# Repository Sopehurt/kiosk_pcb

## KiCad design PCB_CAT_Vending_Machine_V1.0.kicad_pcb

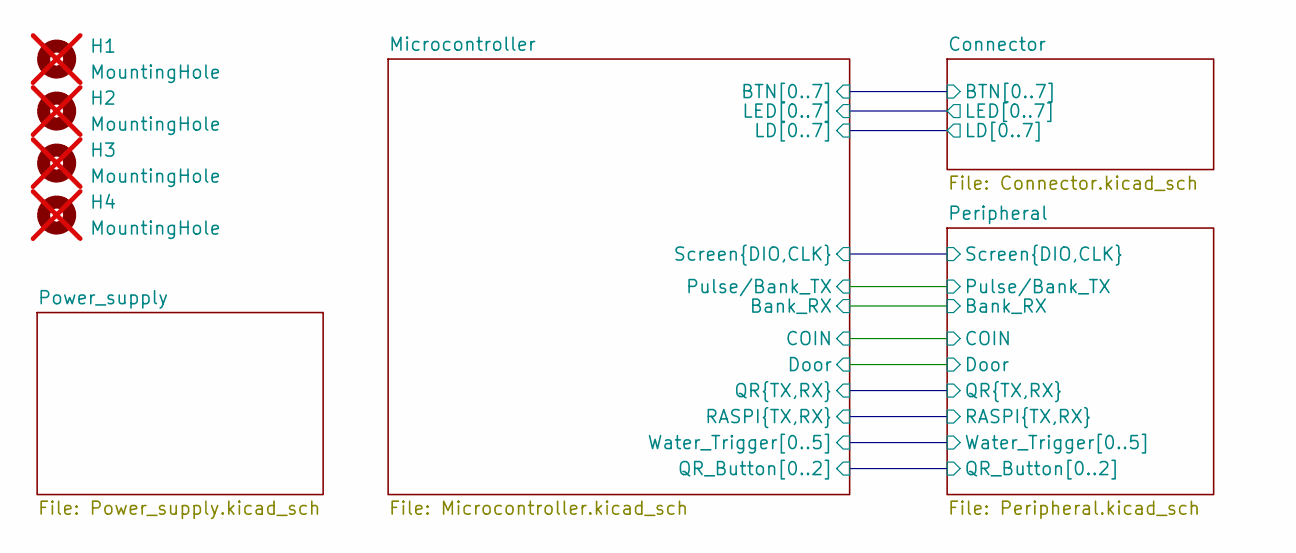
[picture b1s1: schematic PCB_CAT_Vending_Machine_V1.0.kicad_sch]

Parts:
H1, H2, H3, H4: MountingHole; MountingHole_3.2mm_M3_Pad_TopBottom; not fitted

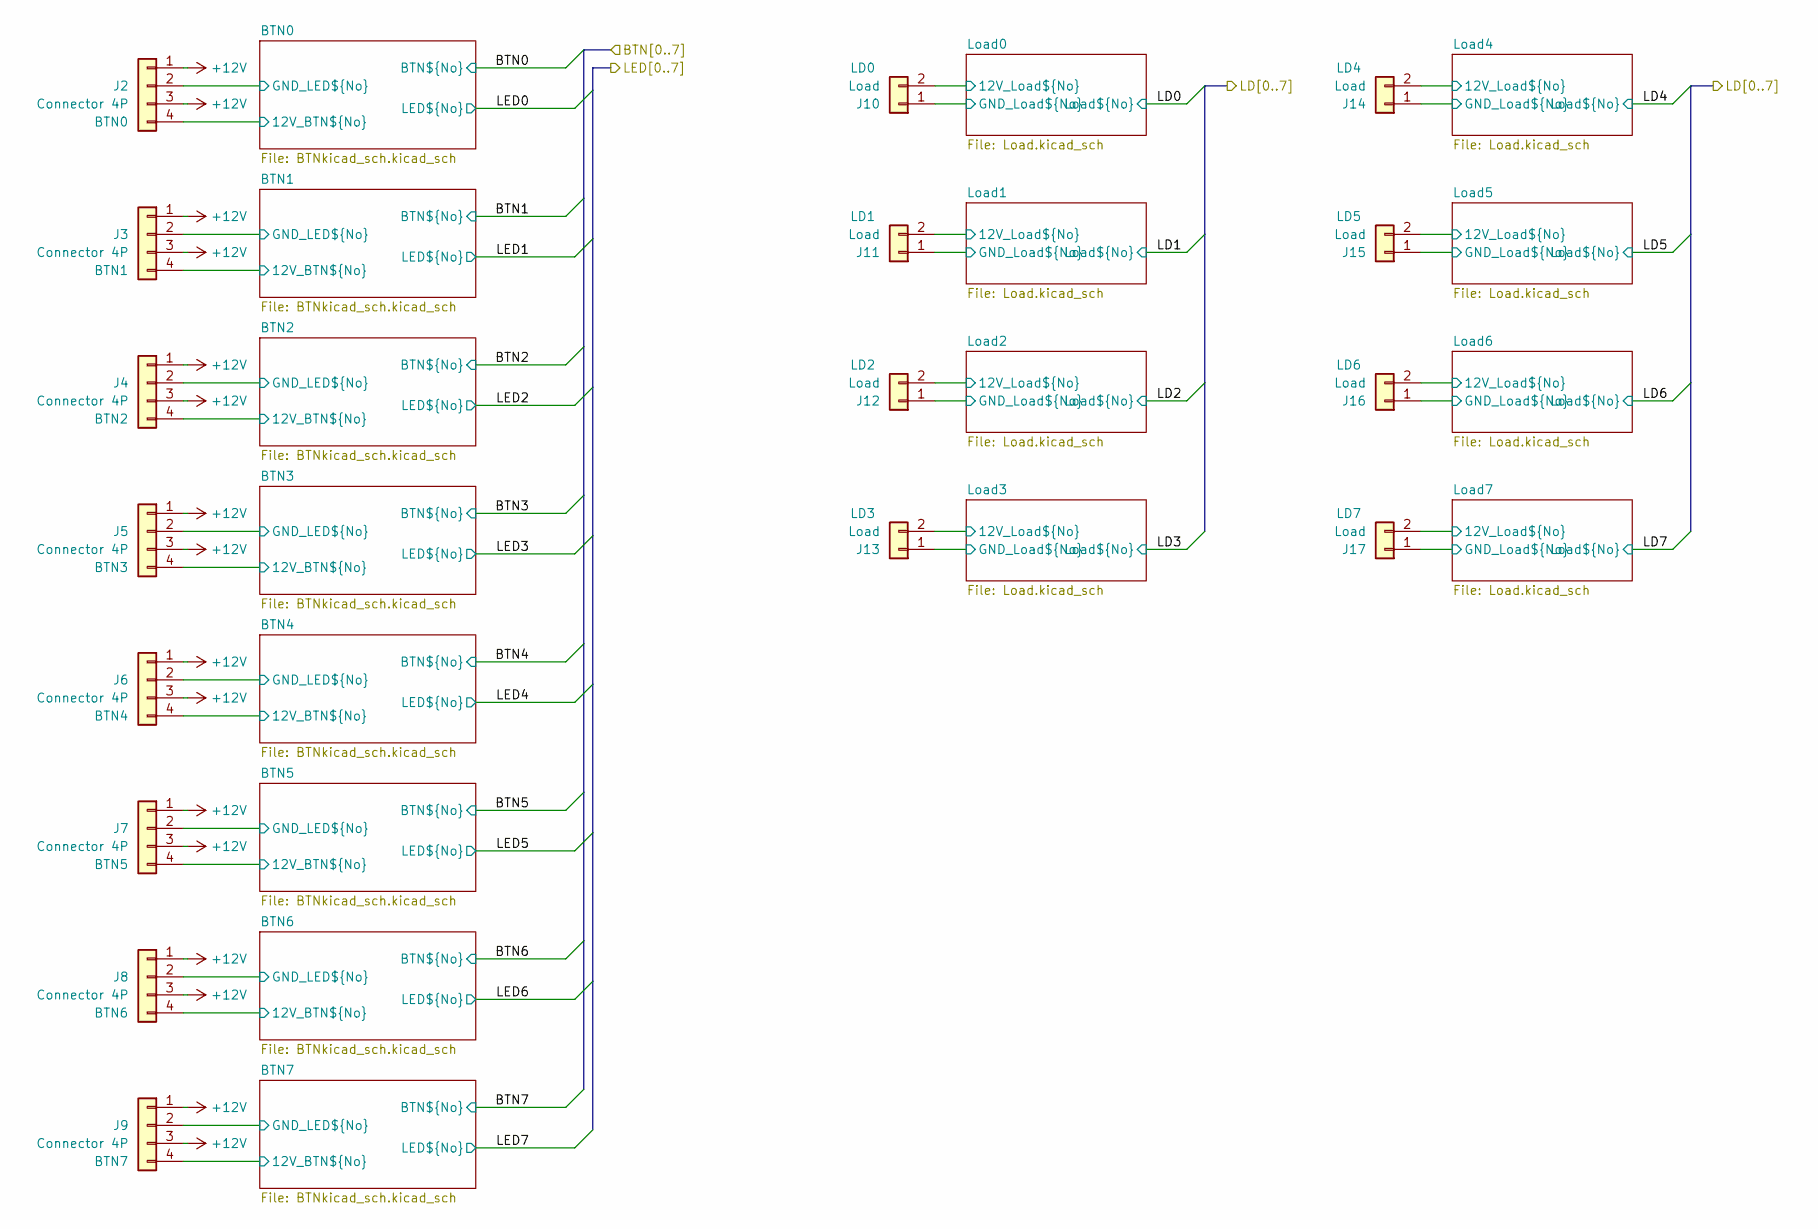
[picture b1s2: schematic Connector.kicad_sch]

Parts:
J2, J3, J4, J5, J6, J7, J8, J9: Connector 4P; JST_XH_B4B-XH-A_1x04_P2.50mm_Vertical; LCSC C7429634
J10, J11, J12, J13, J14, J15, J16, J17: Load; CONN-TH_CH5.08-2A; LCSC C27692

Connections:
+12V: J2.1, J2.3, J3.1, J3.3, J4.1, J4.3, J5.1, J5.3, J6.1, J6.3, J7.1, J7.3, J8.1, J8.3, J9.1, J9.3, J10.2, J11.2, J12.2, J13.2, J14.2, J15.2, J16.2, J17.2; also elsewhere on the board
/Connector/BTN0/12V_BTN0: J2.4; also elsewhere on the board
/Connector/BTN0/GND_LED0: J2.2; also elsewhere on the board
/Connector/BTN1/12V_BTN1: J3.4; also elsewhere on the board
/Connector/BTN1/GND_LED1: J3.2; also elsewhere on the board
/Connector/BTN2/12V_BTN2: J4.4; also elsewhere on the board
/Connector/BTN2/GND_LED2: J4.2; also elsewhere on the board
/Connector/BTN3/12V_BTN3: J5.4; also elsewhere on the board
/Connector/BTN3/GND_LED3: J5.2; also elsewhere on the board
/Connector/BTN4/12V_BTN4: J6.4; also elsewhere on the board
/Connector/BTN4/GND_LED4: J6.2; also elsewhere on the board
/Connector/BTN5/12V_BTN5: J7.4; also elsewhere on the board
/Connector/BTN5/GND_LED5: J7.2; also elsewhere on the board
/Connector/BTN6/12V_BTN6: J8.4; also elsewhere on the board
/Connector/BTN6/GND_LED6: J8.2; also elsewhere on the board
/Connector/BTN7/12V_BTN7: J9.4; also elsewhere on the board
/Connector/BTN7/GND_LED7: J9.2; also elsewhere on the board
/Connector/Load0/GND_Load0: J10.1; also elsewhere on the board
/Connector/Load1/GND_Load1: J11.1; also elsewhere on the board
/Connector/Load2/GND_Load2: J12.1; also elsewhere on the board
/Connector/Load3/GND_Load3: J13.1; also elsewhere on the board
/Connector/Load4/GND_Load4: J14.1; also elsewhere on the board
/Connector/Load5/GND_Load5: J15.1; also elsewhere on the board
/Connector/Load6/GND_Load6: J16.1; also elsewhere on the board
/Connector/Load7/GND_Load7: J17.1; also elsewhere on the board

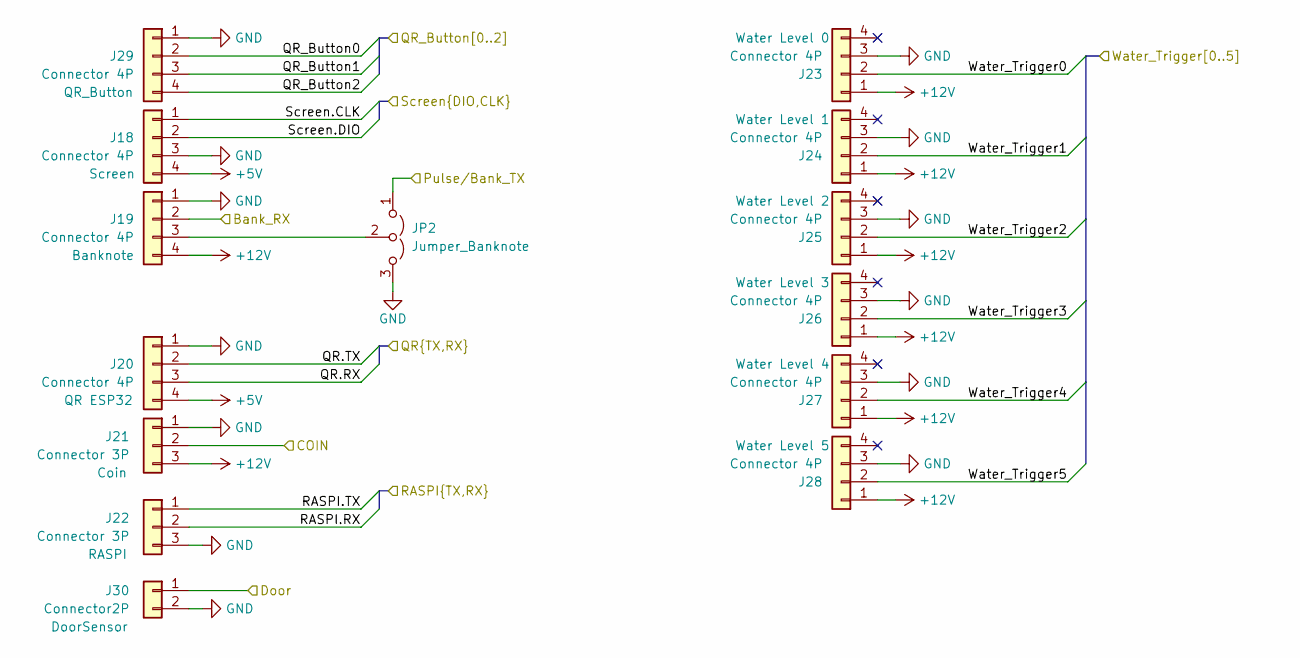
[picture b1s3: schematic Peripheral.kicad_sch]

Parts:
J18, J19, J20, J23, J24, J25, J26, J27, J28, J29: Connector 4P; JST_XH_B4B-XH-A_1x04_P2.50mm_Vertical; LCSC C7429634
J21, J22: Connector 3P; JST_XH_B3B-XH-A_1x03_P2.50mm_Vertical; LCSC C7429633
J30: Connector2P; JST_XH_B2B-XH-A_1x02_P2.50mm_Vertical; LCSC C42441529
JP2: Jumper_Banknote; PinHeader_1x03_P2.54mm_Vertical; LCSC C52016391

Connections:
+5V: J18.4, J20.4; also elsewhere on the board
+12V: J19.4, J21.3, J23.1, J24.1, J25.1, J26.1, J27.1, J28.1; also elsewhere on the board
/Microcontroller/Bank_RX: J19.2; also elsewhere on the board
/Microcontroller/COIN: J21.2; also elsewhere on the board
/Microcontroller/Door: J30.1; also elsewhere on the board
/Microcontroller/Pulse/Bank_TX: JP2.1 (A); also elsewhere on the board
/Microcontroller/QR.RX: J20.3; also elsewhere on the board
/Microcontroller/QR.TX: J20.2; also elsewhere on the board
/Microcontroller/QR_Button0: J29.2; also elsewhere on the board
/Microcontroller/QR_Button1: J29.3; also elsewhere on the board
/Microcontroller/QR_Button2: J29.4; also elsewhere on the board
/Microcontroller/RASPI.RX: J22.2; also elsewhere on the board
/Microcontroller/RASPI.TX: J22.1; also elsewhere on the board
/Microcontroller/Screen.CLK: J18.1; also elsewhere on the board
/Microcontroller/Screen.DIO: J18.2; also elsewhere on the board
/Microcontroller/Water_Trigger0: J23.2; also elsewhere on the board
/Microcontroller/Water_Trigger1: J24.2; also elsewhere on the board
/Microcontroller/Water_Trigger2: J25.2; also elsewhere on the board
/Microcontroller/Water_Trigger3: J26.2; also elsewhere on the board
/Microcontroller/Water_Trigger4: J27.2; also elsewhere on the board
/Microcontroller/Water_Trigger5: J28.2; also elsewhere on the board
GND: J18.3, J19.1, J20.1, J21.1, J22.3, J23.3, J24.3, J25.3, J26.3, J27.3, J28.3, J29.1, J30.2, JP2.3 (B); also elsewhere on the board
unnamed: J19.3, JP2.2 (C)

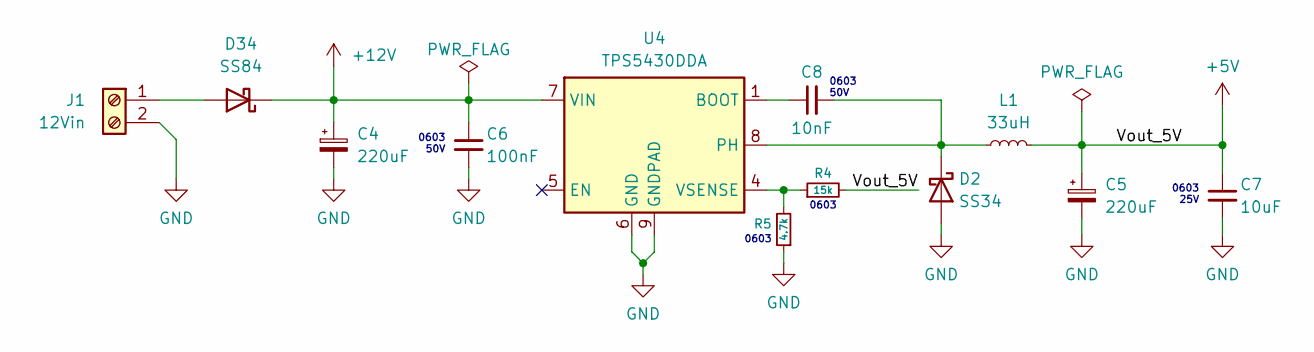
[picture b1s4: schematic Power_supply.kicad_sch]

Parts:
C4, C5: 220uF; CP_Elec_6.3x7.7; LCSC C696188
C6: 100nF; C_0603_1608Metric; LCSC C14663
C7: 10uF; C_0603_1608Metric; LCSC C96446
C8: 10nF; C_0603_1608Metric; LCSC C57112
D2: SS34; D_SMA; LCSC C8678
D34: SS84; D_SMC; JLC C2943761
J1: 12Vin; CONN-TH_2P-P5.00_XY2500V-D-5.00-2P; LCSC C505779
L1: 33uH; L_TechFuse_SL0650; LCSC C5127476
R4: 15k; R_0603_1608Metric; LCSC C22809
R5: 4.7k; R_0603_1608Metric; LCSC C23162
U4: TPS5430DDA; TI_SO-PowerPAD-8_ThermalVias; LCSC C9864

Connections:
+5V: C5.1, C7.1, L1.2, R4.2; also elsewhere on the board
+12V: C4.1, C6.1, D34.1 (K), U4.7 (VIN); also elsewhere on the board
GND: C4.2, C5.2, C6.2, C7.2, D2.2 (A), J1.2, R5.1, U4.6 (GND), U4.9 (GNDPAD); also elsewhere on the board
unnamed: C8.2, D2.1 (K), L1.1, U4.8 (PH)
unnamed: D34.2 (A), J1.1
unnamed: C8.1, U4.1 (BOOT)
unnamed: R4.1, R5.2, U4.4 (VSENSE)

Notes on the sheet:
0603 50V
0603 25V
0603

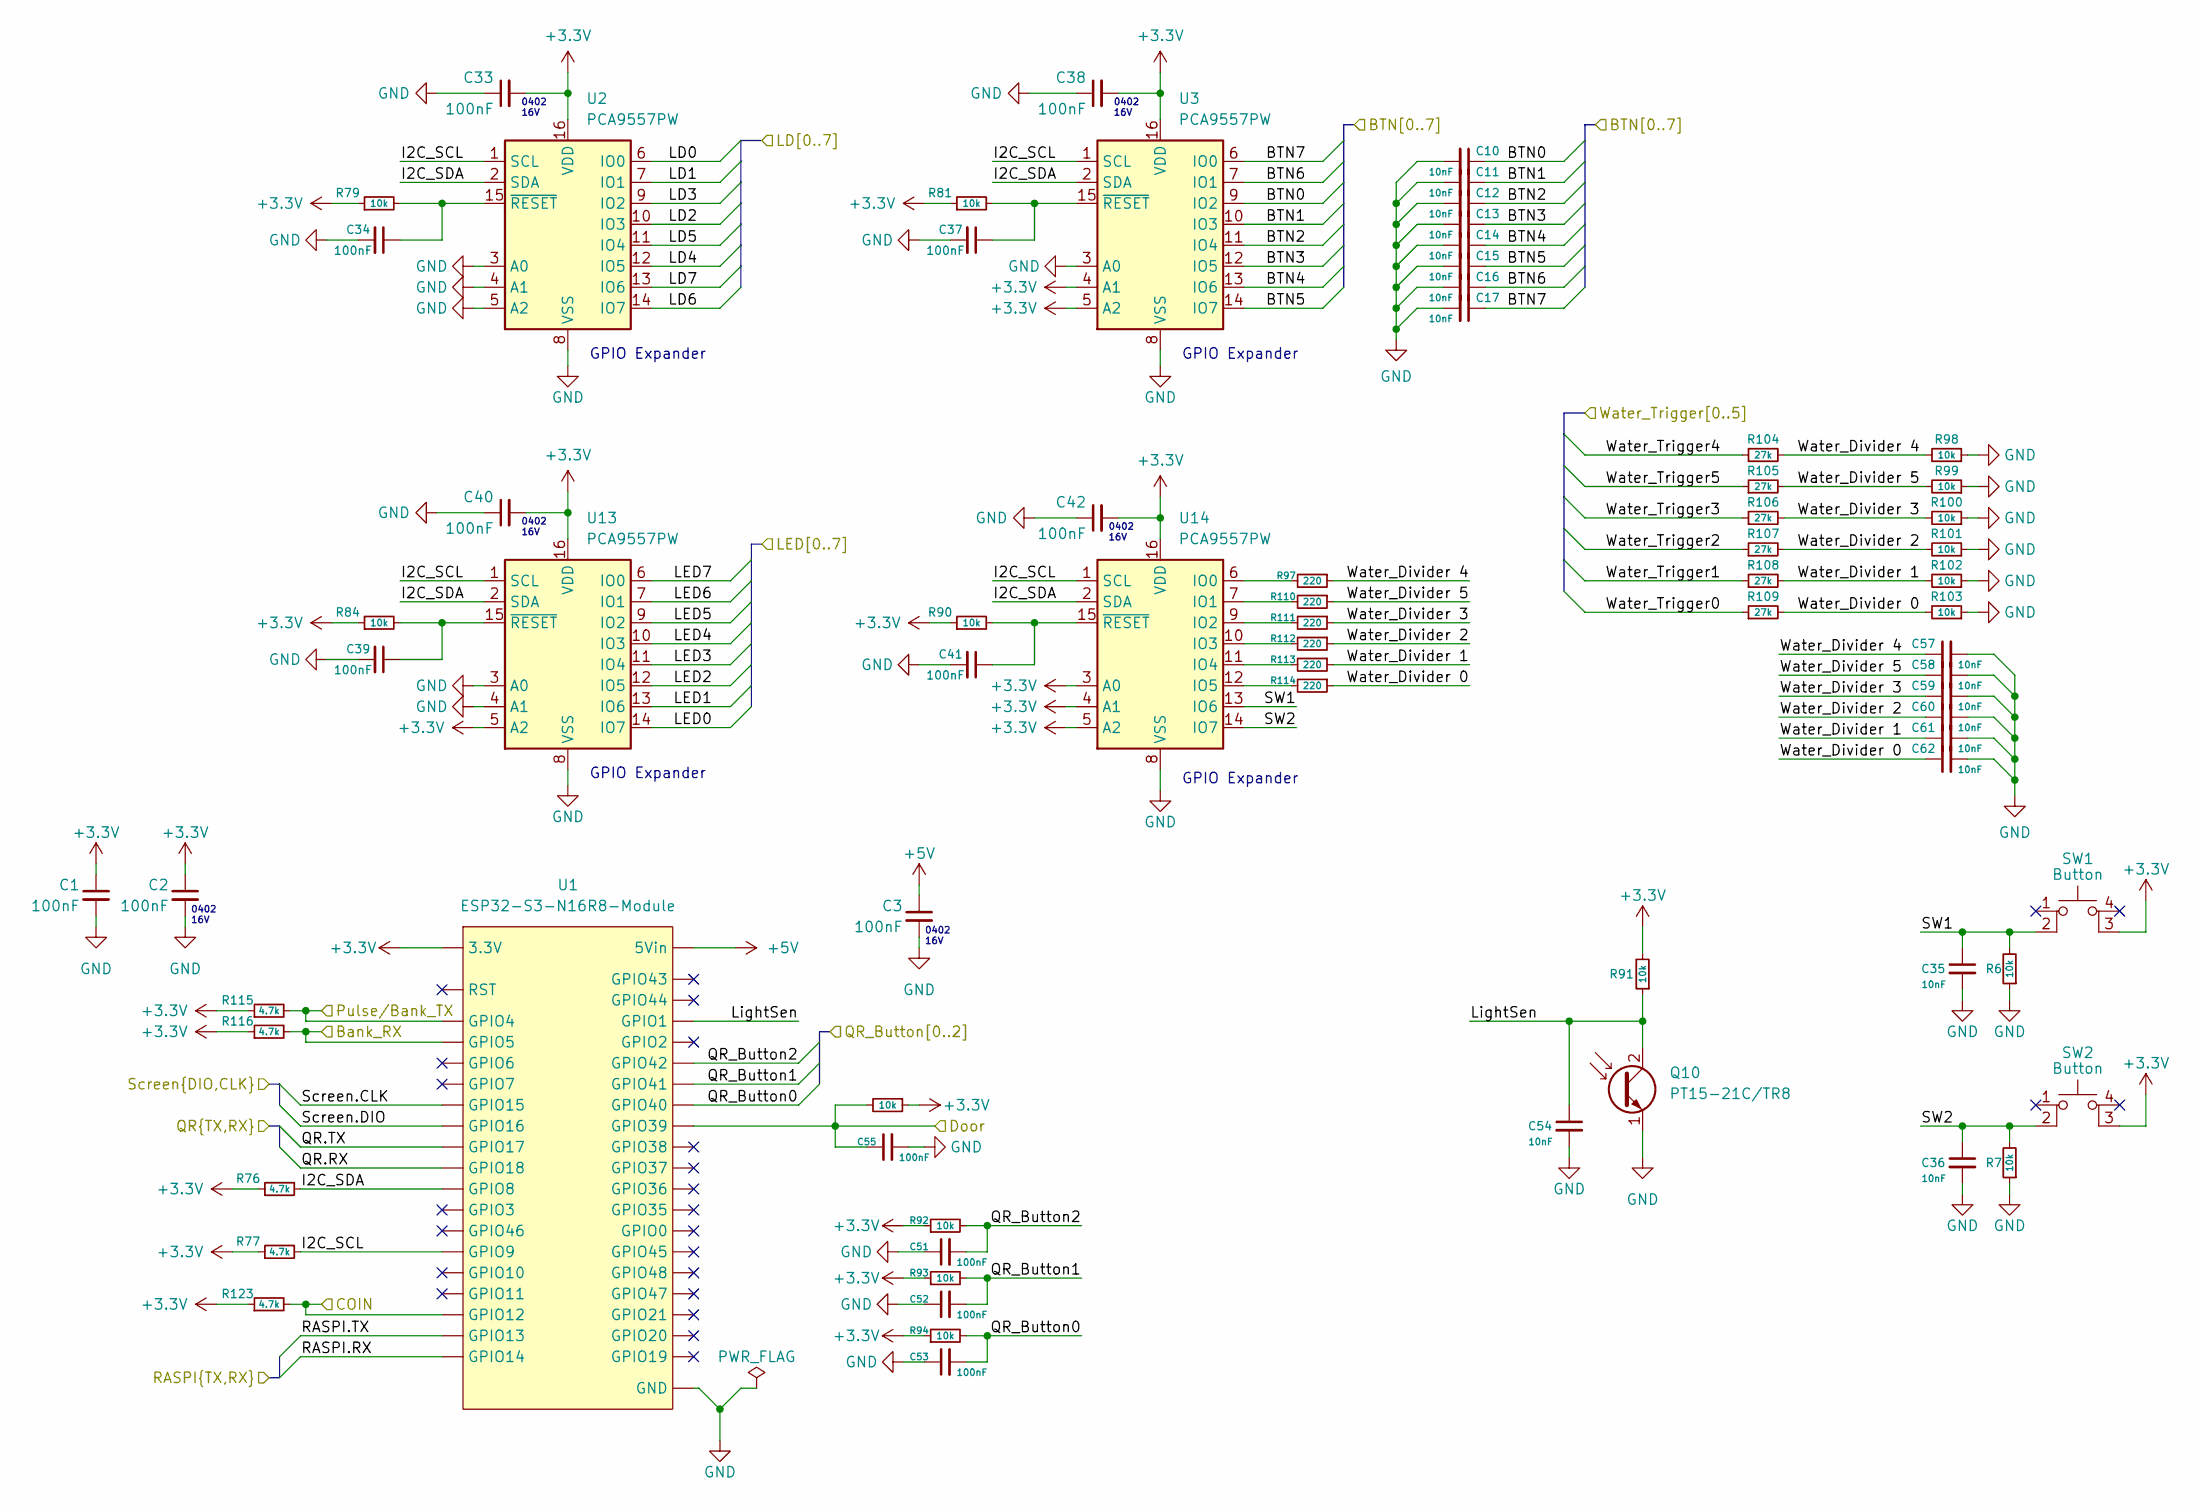
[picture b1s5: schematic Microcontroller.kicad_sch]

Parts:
C1, C2, C3, C33, C34, C37, C38, C39, C40, C41, C42, C51, C52, C53, C55: 100nF; C_0402_1005Metric; LCSC C1525
C10, C11, C12, C13, C14, C15, C16, C17, C35, C36, C54, C57, C58, C59, C60, C61, C62: 10nF; C_0402_1005Metric; LCSC C15195
Q10: PT15-21C/TR8; LED_1206_3216Metric; LCSC C41383389
R6, R7, R79, R81, R84, R90, R91, R92, R93, R94, R95, R98, R99, R100, R101, R102, R103: 10k; R_0402_1005Metric; LCSC C25744
R76, R77, R115, R116, R123: 4.7k; R_0402_1005Metric; LCSC C25900
R97, R110, R111, R112, R113, R114: 220; R_0402_1005Metric; LCSC C25091
R104, R105, R106, R107, R108, R109: 27k; R_0603_1608Metric; LCSC C22967
SW1, SW2: Button; 430182043816; LCSC C5340127
U1: ESP32-S3-N16R8-Module; ESP32-S3 N16R8-Module
U2, U3, U13, U14: PCA9557PW; TSSOP-16_4.4x5mm_P0.65mm; LCSC C141380

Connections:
+3.3V: C1.1, C2.1, C33.2, C38.2, C40.2, C42.2, R76.1, R77.1, R79.1, R81.1, R84.1, R90.1, R91.2, R92.1, R93.1, R94.1, R95.1, R115.1, R116.1, R123.1, SW1.3 (K), SW2.3 (K), U1.1 (3.3V), U1.2 (3.3V), U2.16 (VDD), U3.4 (A1), U3.5 (A2), U3.16 (VDD), U13.5 (A2), U13.16 (VDD), U14.3 (A0), U14.4 (A1), U14.5 (A2), U14.16 (VDD); also elsewhere on the board
+5V: C3.1, U1.21 (5Vin); also elsewhere on the board
/Connector/BTN0: C10.1, U3.9 (IO2); also elsewhere on the board
/Connector/BTN1: C11.1, U3.10 (IO3); also elsewhere on the board
/Connector/BTN2: C12.1, U3.11 (IO4); also elsewhere on the board
/Connector/BTN3: C13.1, U3.12 (IO5); also elsewhere on the board
/Connector/BTN4: C14.1, U3.13 (IO6); also elsewhere on the board
/Connector/BTN5: C15.1, U3.14 (IO7); also elsewhere on the board
/Connector/BTN6: C16.1, U3.7 (IO1); also elsewhere on the board
/Connector/BTN7: C17.1, U3.6 (IO0); also elsewhere on the board
/Connector/LD0: U2.6 (IO0); also elsewhere on the board
/Connector/LD1: U2.7 (IO1); also elsewhere on the board
/Connector/LD2: U2.10 (IO3); also elsewhere on the board
/Connector/LD3: U2.9 (IO2); also elsewhere on the board
/Connector/LD4: U2.12 (IO5); also elsewhere on the board
/Connector/LD5: U2.11 (IO4); also elsewhere on the board
/Connector/LD6: U2.14 (IO7); also elsewhere on the board
/Connector/LD7: U2.13 (IO6); also elsewhere on the board
/Connector/LED0: U13.14 (IO7); also elsewhere on the board
/Connector/LED1: U13.13 (IO6); also elsewhere on the board
/Connector/LED2: U13.12 (IO5); also elsewhere on the board
/Connector/LED3: U13.11 (IO4); also elsewhere on the board
/Connector/LED4: U13.10 (IO3); also elsewhere on the board
/Connector/LED5: U13.9 (IO2); also elsewhere on the board
/Connector/LED6: U13.7 (IO1); also elsewhere on the board
/Connector/LED7: U13.6 (IO0); also elsewhere on the board
/Microcontroller/Bank_RX: R116.2, U1.5 (GPIO5); also elsewhere on the board
/Microcontroller/COIN: R123.2, U1.18 (GPIO12); also elsewhere on the board
/Microcontroller/Door: C55.1, R95.2, U1.36 (GPIO39); also elsewhere on the board
/Microcontroller/I2C_SCL: R77.2, U1.15 (GPIO9), U2.1 (SCL), U3.1 (SCL), U13.1 (SCL), U14.1 (SCL)
/Microcontroller/I2C_SDA: R76.2, U1.12 (GPIO8), U2.2 (SDA), U3.2 (SDA), U13.2 (SDA), U14.2 (SDA)
/Microcontroller/LightSen: C54.1, Q10.2 (C), R91.1, U1.41 (GPIO1)
/Microcontroller/Pulse/Bank_TX: R115.2, U1.4 (GPIO4); also elsewhere on the board
/Microcontroller/QR.RX: U1.11 (GPIO18); also elsewhere on the board
/Microcontroller/QR.TX: U1.10 (GPIO17); also elsewhere on the board
/Microcontroller/QR_Button0: C53.2, R94.2, U1.37 (GPIO40); also elsewhere on the board
/Microcontroller/QR_Button1: C52.2, R93.2, U1.38 (GPIO41); also elsewhere on the board
/Microcontroller/QR_Button2: C51.2, R92.2, U1.39 (GPIO42); also elsewhere on the board
/Microcontroller/RASPI.RX: U1.20 (GPIO14); also elsewhere on the board
/Microcontroller/RASPI.TX: U1.19 (GPIO13); also elsewhere on the board
/Microcontroller/SW1: C35.1, R6.2, SW1.2, U14.13 (IO6)
/Microcontroller/SW2: C36.1, R7.2, SW2.2, U14.14 (IO7)
/Microcontroller/Screen.CLK: U1.8 (GPIO15); also elsewhere on the board
/Microcontroller/Screen.DIO: U1.9 (GPIO16); also elsewhere on the board
/Microcontroller/Water_Divider 0: C62.1, R103.2, R109.2, R114.1
/Microcontroller/Water_Divider 1: C61.1, R102.2, R108.2, R113.1
/Microcontroller/Water_Divider 2: C60.1, R101.2, R107.2, R112.1
/Microcontroller/Water_Divider 3: C59.1, R100.2, R106.2, R111.1
/Microcontroller/Water_Divider 4: C57.1, R97.1, R98.2, R104.2
/Microcontroller/Water_Divider 5: C58.1, R99.2, R105.2, R110.1
/Microcontroller/Water_Trigger0: R109.1; also elsewhere on the board
/Microcontroller/Water_Trigger1: R108.1; also elsewhere on the board
/Microcontroller/Water_Trigger2: R107.1; also elsewhere on the board
/Microcontroller/Water_Trigger3: R106.1; also elsewhere on the board
/Microcontroller/Water_Trigger4: R104.1; also elsewhere on the board
/Microcontroller/Water_Trigger5: R105.1; also elsewhere on the board
GND: C1.2, C2.2, C3.2, C10.2, C11.2, C12.2, C13.2, C14.2, C15.2, C16.2, C17.2, C33.1, C34.2, C35.2, C36.2, C37.2, C38.1, C39.2, C40.1, C41.2, C42.1, C51.1, C52.1, C53.1, C54.2, C55.2, C57.2, C58.2, C59.2, C60.2, C61.2, C62.2, Q10.1 (E), R6.1, R7.1, R98.1, R99.1, R100.1, R101.1, R102.1, R103.1, U1.22 (GND), U1.23 (GND), U1.24 (GND), U1.44 (GND), U2.3 (A0), U2.4 (A1), U2.5 (A2), U2.8 (VSS), U3.3 (A0), U3.8 (VSS), U13.3 (A0), U13.4 (A1), U13.8 (VSS), U14.8 (VSS); also elsewhere on the board
unnamed: C34.1, R79.2, U2.15 (~RESET)
unnamed: C37.1, R81.2, U3.15 (~RESET)
unnamed: C39.1, R84.2, U13.15 (~RESET)
unnamed: R97.2, U14.6 (IO0)
unnamed: R110.2, U14.7 (IO1)
unnamed: R111.2, U14.9 (IO2)
unnamed: R112.2, U14.10 (IO3)
unnamed: R113.2, U14.11 (IO4)
unnamed: R114.2, U14.12 (IO5)
unnamed: C41.1, R90.2, U14.15 (~RESET)

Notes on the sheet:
GPIO Expander
0402 16V

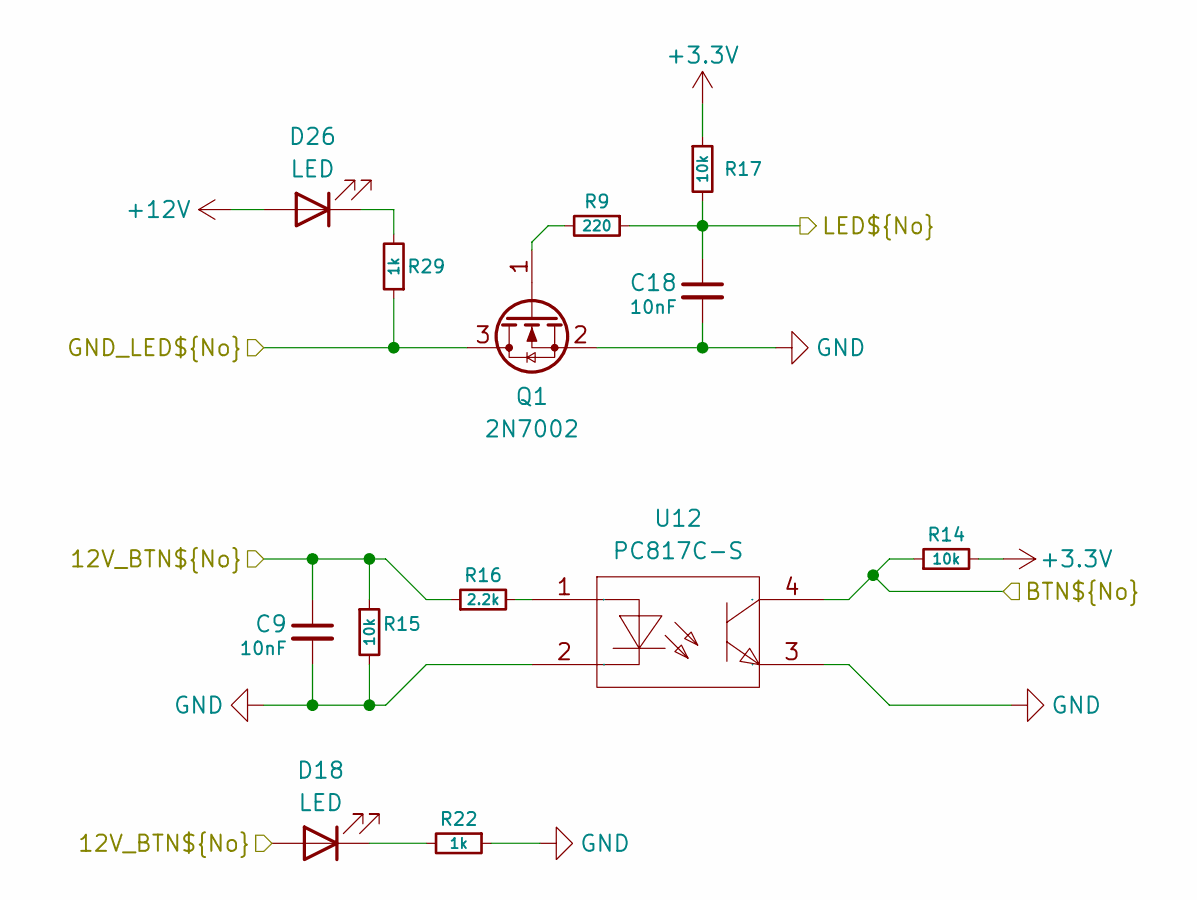
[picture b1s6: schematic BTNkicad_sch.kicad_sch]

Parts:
C9, C18: 10nF; C_0402_1005Metric; LCSC C15195
D18, D26: LED; LED_0603_1608Metric; LCSC C2290
Q1: 2N7002; SOT-23; LCSC C8545
R9: 220; R_0402_1005Metric; LCSC C25091
R14, R15, R17: 10k; R_0402_1005Metric; LCSC C25744
R16: 2.2k; R_0402_1005Metric; LCSC C25879
R22, R29: 1k; R_0402_1005Metric; LCSC C4109
U12: PC817C-S; SOP-4_L6.5-W4.6-P2.54-LS10.3-TL; Manufacturer Part PC817C-S; LCSC Part Name 光耦合器

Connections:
+3.3V: R14.2, R17.1; also elsewhere on the board
+12V: D26.2 (A); also elsewhere on the board
/Connector/BTN0: R14.1, U12.4 (COL); also elsewhere on the board
/Connector/BTN0/12V_BTN0: C9.1, D18.2 (A), R15.1, R16.1; also elsewhere on the board
/Connector/BTN0/GND_LED0: Q1.3 (D), R29.1; also elsewhere on the board
/Connector/LED0: C18.1, R9.1, R17.2; also elsewhere on the board
GND: C9.2, C18.2, Q1.2 (S), R15.2, R22.1, U12.2 (CAT), U12.3 (EM); also elsewhere on the board
unnamed: D18.1 (K), R22.2
unnamed: D26.1 (K), R29.2
unnamed: Q1.1 (G), R9.2
unnamed: R16.2, U12.1 (AN)

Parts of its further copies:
C19, C20, C21, C22, C23, C24, C25, C26, C27, C28, C29, C30, C31, C32: 10nF; C_0402_1005Metric; LCSC C15195
D19, D20, D21, D22, D23, D24, D25, D27, D28, D29, D30, D31, D32, D33: LED; LED_0603_1608Metric; LCSC C2290
Q2, Q4, Q5, Q6, Q7, Q8, Q9: 2N7002; SOT-23; LCSC C8545
R18, R21, R23, R24, R27, R45, R46, R49, R51, R52, R55, R57, R58, R61, R63, R64, R67, R69, R70, R73, R75: 10k; R_0402_1005Metric; LCSC C25744
R19, R25, R47, R53, R59, R65, R71: 2.2k; R_0402_1005Metric; LCSC C25879
R20, R26, R48, R54, R60, R66, R72: 220; R_0402_1005Metric; LCSC C25091
R31, R33, R35, R37, R39, R41, R43, R44, R50, R56, R62, R68, R74, R78: 1k; R_0402_1005Metric; LCSC C4109
U5, U6, U7, U8, U9, U10, U11: PC817C-S; SOP-4_L6.5-W4.6-P2.54-LS10.3-TL; Manufacturer Part PC817C-S; LCSC Part Name 光耦合器

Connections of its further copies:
+3.3V: R21.1, R23.2, R27.1, R45.2, R49.1, R51.2, R55.1, R57.2, R61.1, R63.2, R67.1, R69.2, R73.1, R75.2; also elsewhere on the board
+12V: D27.2 (A), D28.2 (A), D29.2 (A), D30.2 (A), D31.2 (A), D32.2 (A), D33.2 (A); also elsewhere on the board
/Connector/BTN1: R23.1, U5.4 (COL); also elsewhere on the board
/Connector/BTN1/12V_BTN1: C19.1, D19.2 (A), R18.1, R19.1; also elsewhere on the board
/Connector/BTN1/GND_LED1: Q2.3 (D), R31.1; also elsewhere on the board
/Connector/BTN2: R45.1, U6.4 (COL); also elsewhere on the board
/Connector/BTN2/12V_BTN2: C21.1, D20.2 (A), R24.1, R25.1; also elsewhere on the board
/Connector/BTN2/GND_LED2: Q4.3 (D), R33.1; also elsewhere on the board
/Connector/BTN3: R51.1, U7.4 (COL); also elsewhere on the board
/Connector/BTN3/12V_BTN3: C23.1, D21.2 (A), R46.1, R47.1; also elsewhere on the board
/Connector/BTN3/GND_LED3: Q5.3 (D), R35.1; also elsewhere on the board
/Connector/BTN4: R57.1, U8.4 (COL); also elsewhere on the board
/Connector/BTN4/12V_BTN4: C25.1, D22.2 (A), R52.1, R53.1; also elsewhere on the board
/Connector/BTN4/GND_LED4: Q6.3 (D), R37.1; also elsewhere on the board
/Connector/BTN5: R63.1, U9.4 (COL); also elsewhere on the board
/Connector/BTN5/12V_BTN5: C27.1, D23.2 (A), R58.1, R59.1; also elsewhere on the board
/Connector/BTN5/GND_LED5: Q7.3 (D), R39.1; also elsewhere on the board
/Connector/BTN6: R69.1, U10.4 (COL); also elsewhere on the board
/Connector/BTN6/12V_BTN6: C29.1, D24.2 (A), R64.1, R65.1; also elsewhere on the board
/Connector/BTN6/GND_LED6: Q8.3 (D), R41.1; also elsewhere on the board
/Connector/BTN7: R75.1, U11.4 (COL); also elsewhere on the board
/Connector/BTN7/12V_BTN7: C31.1, D25.2 (A), R70.1, R71.1; also elsewhere on the board
/Connector/BTN7/GND_LED7: Q9.3 (D), R43.1; also elsewhere on the board
/Connector/LED1: C20.1, R20.1, R21.2; also elsewhere on the board
/Connector/LED2: C22.1, R26.1, R27.2; also elsewhere on the board
/Connector/LED3: C24.1, R48.1, R49.2; also elsewhere on the board
/Connector/LED4: C26.1, R54.1, R55.2; also elsewhere on the board
/Connector/LED5: C28.1, R60.1, R61.2; also elsewhere on the board
/Connector/LED6: C30.1, R66.1, R67.2; also elsewhere on the board
/Connector/LED7: C32.1, R72.1, R73.2; also elsewhere on the board
GND: C19.2, C20.2, C21.2, C22.2, C23.2, C24.2, C25.2, C26.2, C27.2, C28.2, C29.2, C30.2, C31.2, C32.2, Q2.2 (S), Q4.2 (S), Q5.2 (S), Q6.2 (S), Q7.2 (S), Q8.2 (S), Q9.2 (S), R18.2, R24.2, R44.1, R46.2, R50.1, R52.2, R56.1, R58.2, R62.1, R64.2, R68.1, R70.2, R74.1, R78.1, U5.2 (CAT), U5.3 (EM), U6.2 (CAT), U6.3 (EM), U7.2 (CAT), U7.3 (EM), U8.2 (CAT), U8.3 (EM), U9.2 (CAT), U9.3 (EM), U10.2 (CAT), U10.3 (EM), U11.2 (CAT), U11.3 (EM); also elsewhere on the board
unnamed: D19.1 (K), R44.2
unnamed: D20.1 (K), R50.2
unnamed: D21.1 (K), R56.2
unnamed: D22.1 (K), R62.2
unnamed: D23.1 (K), R68.2
unnamed: D24.1 (K), R74.2
unnamed: D25.1 (K), R78.2
unnamed: D27.1 (K), R31.2
unnamed: D28.1 (K), R33.2
unnamed: D29.1 (K), R35.2
unnamed: D30.1 (K), R37.2
unnamed: D31.1 (K), R39.2
unnamed: D32.1 (K), R41.2
unnamed: D33.1 (K), R43.2
unnamed: Q2.1 (G), R20.2
unnamed: Q4.1 (G), R26.2
unnamed: Q5.1 (G), R48.2
unnamed: Q6.1 (G), R54.2
unnamed: Q7.1 (G), R60.2
unnamed: Q8.1 (G), R66.2
unnamed: Q9.1 (G), R72.2
unnamed: R19.2, U5.1 (AN)
unnamed: R25.2, U6.1 (AN)
unnamed: R47.2, U7.1 (AN)
unnamed: R53.2, U8.1 (AN)
unnamed: R59.2, U9.1 (AN)
unnamed: R65.2, U10.1 (AN)
unnamed: R71.2, U11.1 (AN)

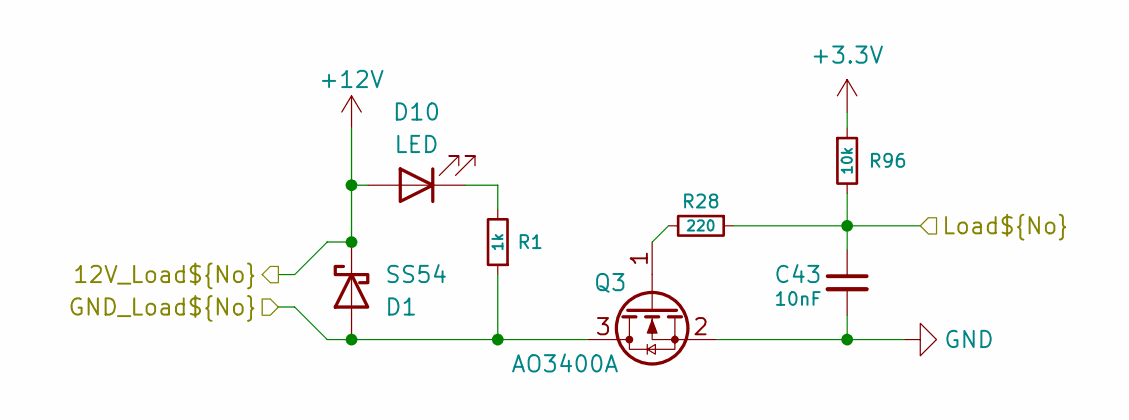
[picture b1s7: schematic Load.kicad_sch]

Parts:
C43: 10nF; C_0402_1005Metric; LCSC C15195
D1: SS54; D_SMA; LCSC C22452
D10: LED; LED_0603_1608Metric; LCSC C2290
Q3: AO3400A; SOT-23; LCSC C20917
R1: 1k; R_0402_1005Metric; LCSC C4109
R28: 220; R_0402_1005Metric; LCSC C25091
R96: 10k; R_0402_1005Metric; LCSC C25744

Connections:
+3.3V: R96.1; also elsewhere on the board
+12V: D1.1 (K), D10.2 (A); also elsewhere on the board
/Connector/LD0: C43.1, R28.1, R96.2; also elsewhere on the board
/Connector/Load0/GND_Load0: D1.2 (A), Q3.3 (D), R1.1; also elsewhere on the board
GND: C43.2, Q3.2 (S); also elsewhere on the board
unnamed: D10.1 (K), R1.2
unnamed: Q3.1 (G), R28.2

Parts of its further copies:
C44, C45, C46, C47, C48, C49, C50: 10nF; C_0402_1005Metric; LCSC C15195
D3, D4, D5, D6, D7, D8, D9: SS54; D_SMA; LCSC C22452
D11, D12, D13, D14, D15, D16, D17: LED; LED_0603_1608Metric; LCSC C2290
Q12, Q13, Q14, Q15, Q16, Q17, Q18: AO3400A; SOT-23; LCSC C20917
R2, R3, R8, R10, R11, R12, R13: 1k; R_0402_1005Metric; LCSC C4109
R30, R32, R34, R36, R38, R40, R42: 220; R_0402_1005Metric; LCSC C25091
R117, R118, R119, R120, R121, R122, R124: 10k; R_0402_1005Metric; LCSC C25744

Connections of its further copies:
+3.3V: R117.1, R118.1, R119.1, R120.1, R121.1, R122.1, R124.1; also elsewhere on the board
+12V: D3.1 (K), D4.1 (K), D5.1 (K), D6.1 (K), D7.1 (K), D8.1 (K), D9.1 (K), D11.2 (A), D12.2 (A), D13.2 (A), D14.2 (A), D15.2 (A), D16.2 (A), D17.2 (A); also elsewhere on the board
/Connector/LD1: C44.1, R30.1, R117.2; also elsewhere on the board
/Connector/LD2: C45.1, R32.1, R118.2; also elsewhere on the board
/Connector/LD3: C46.1, R34.1, R119.2; also elsewhere on the board
/Connector/LD4: C47.1, R36.1, R120.2; also elsewhere on the board
/Connector/LD5: C48.1, R38.1, R121.2; also elsewhere on the board
/Connector/LD6: C49.1, R40.1, R122.2; also elsewhere on the board
/Connector/LD7: C50.1, R42.1, R124.2; also elsewhere on the board
/Connector/Load1/GND_Load1: D3.2 (A), Q12.3 (D), R2.1; also elsewhere on the board
/Connector/Load2/GND_Load2: D4.2 (A), Q13.3 (D), R3.1; also elsewhere on the board
/Connector/Load3/GND_Load3: D5.2 (A), Q14.3 (D), R8.1; also elsewhere on the board
/Connector/Load4/GND_Load4: D6.2 (A), Q15.3 (D), R10.1; also elsewhere on the board
/Connector/Load5/GND_Load5: D7.2 (A), Q16.3 (D), R11.1; also elsewhere on the board
/Connector/Load6/GND_Load6: D8.2 (A), Q17.3 (D), R12.1; also elsewhere on the board
/Connector/Load7/GND_Load7: D9.2 (A), Q18.3 (D), R13.1; also elsewhere on the board
GND: C44.2, C45.2, C46.2, C47.2, C48.2, C49.2, C50.2, Q12.2 (S), Q13.2 (S), Q14.2 (S), Q15.2 (S), Q16.2 (S), Q17.2 (S), Q18.2 (S); also elsewhere on the board
unnamed: D11.1 (K), R2.2
unnamed: D12.1 (K), R3.2
unnamed: D13.1 (K), R8.2
unnamed: D14.1 (K), R10.2
unnamed: D15.1 (K), R11.2
unnamed: D16.1 (K), R12.2
unnamed: D17.1 (K), R13.2
unnamed: Q12.1 (G), R30.2
unnamed: Q13.1 (G), R32.2
unnamed: Q14.1 (G), R34.2
unnamed: Q15.1 (G), R36.2
unnamed: Q16.1 (G), R38.2
unnamed: Q17.1 (G), R40.2
unnamed: Q18.1 (G), R42.2
